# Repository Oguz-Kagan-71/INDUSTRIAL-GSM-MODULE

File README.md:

# INDUSTRIAL-GSM-MODULE
**PROJE KAZANIMLARI**
- Farklı amaca hizmet eden modüllerin datasheetini okuma
- Projeye uygun modül ve komponent seçimi
- Beslemelerde koruma amaçlı kullanılan kapasitör, endüktör, tvs diyot vb komponentlerin kullanımı
- PCB design edilen programda çoklu şematik pencere kullanımı, global label vb özelliklerin aktif kullanımı
- Kütüphanede olmayan komponentlerin şematik ve footprint kütüphanelerini datasheet bilgilerine göre oluşturup ekleme
- RS485 iletişim standartının ne olduğu ve hangi alanda kullanıldığı
- Transciever nedir ? Nasıl kullanılır ?
- Buck converter nedir ? Nasıl tasarlanır ?
- Yüksek voltaj kullanılan bir projede tasarım nasıl olmalıdır ? Regüle edilirken kullanılan komponentler nasıl konumlandırılmalıdır ?
- Konnektörler nasıl konumlandırılmalıdır ?
- Bağlantı kalınlıkları nasıl olmalıdır ?
- Anten bağlantısı nasıl olmalıdır ?
- Haberleşme bağlantıları nasıl olmalıdır ?
- GSM modülü nasıl çalışır ? Hangi amaca hizmet eder ?
- Modbus protokolü nedir ? Diğer haberleşme türlerinden farkı nedir ?
- 
-

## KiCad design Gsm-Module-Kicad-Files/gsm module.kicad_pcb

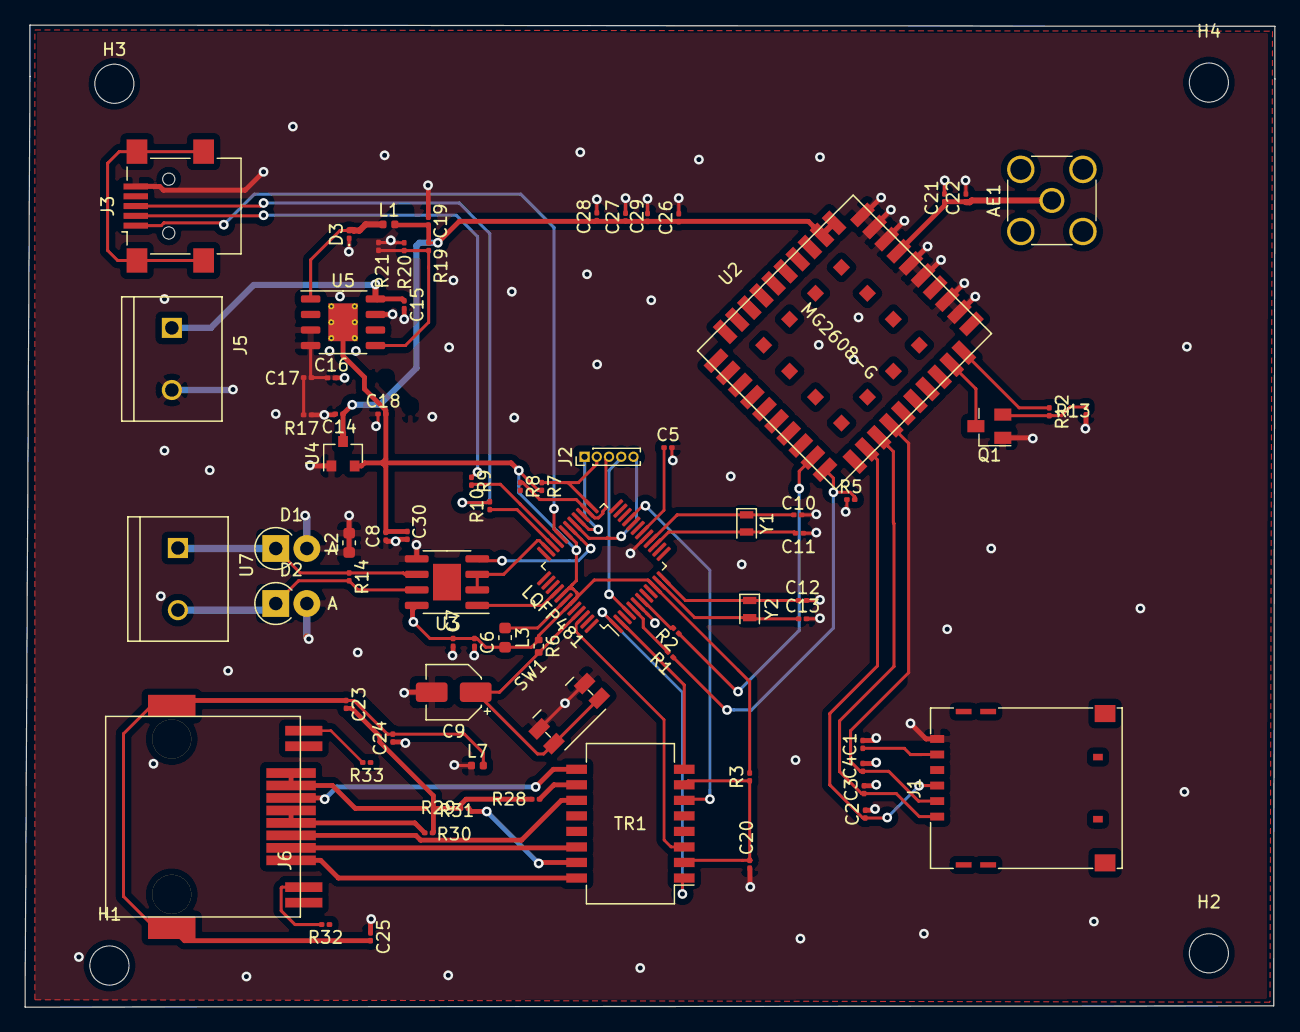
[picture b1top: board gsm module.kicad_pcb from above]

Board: 2 copper layers, 102.2 x 80.3 mm, 80 parts (0 on the bottom side), 59 nets.

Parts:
AE1: Antenna; SMA_Amphenol_132291_Vertical
C1: 0.1u; C_0201_0603Metric
C2, C3, C4, C21, C22, C29: 33p; C_0201_0603Metric
C5, C6, C7, C8: 0.1uF; C_0201_0603Metric
C9: 10uF/10V; CP_Elec_4x3
C10, C11, C12, C13: 20p; C_0201_0603Metric
C14, C18: 220nF; C_0201_0603Metric
C15: 10uF; C_0201_0603Metric
C16: 220uF; C_0201_0603Metric
C17: 22nF; C_0201_0603Metric
C19: 330uF; C_0201_0603Metric
C20: 220n; C_0201_0603Metric
C23: 1nF; C_0201_0603Metric
C24, C25: 100uF; C_0201_0603Metric
C26: 100u; C_0201_0603Metric
C27: 100n; C_0201_0603Metric
C28: 10p; C_0201_0603Metric
C30: 10u; C_0201_0603Metric
D1, D2: D_Schottky; D_DO-41_SOD81_P2.54mm_Vertical_AnodeUp
D3: DIODE; D_0201_0603Metric
H1, H2, H3, H4: MountingHole; MountingHole_3.2mm_M3
J1: SIM_Card; microSIM_JAE_SF53S006VCBR2000
J2: Conn_01x05_Male; PinHeader_1x05_P1.00mm_Vertical
J3: USB_OTG; USB_Mini-B_Lumberg_2486_01_Horizontal
J5: Conn_01x02_Male; TE_282837-2
J6: 8P8C_LED_Shielded; Würth_RJ45_SMD
L1: 33H; L_0402_1005Metric
L2, L3: L_Ferrite; L_0603_1608Metric
L7: 3H; L_0402_1005Metric
LQFP481: NUC126LG4AE; LQFP-48_7x7mm_P0.5mm
Q1: 2N2219; SuperSOT-3
R1, R2: 1k; R_0201_0603Metric
R3: 0; R_0201_0603Metric
R5: 5.6K; R_0201_0603Metric
R6: 10K; R_0402_1005Metric
R7, R8: 100K; R_0201_0603Metric
R9, R10: 33R; R_0201_0603Metric
R12, R17, R20, R21: 4.7k; R_0201_0603Metric
R13: 47k; R_0201_0603Metric
R14: 120R; R_0201_0603Metric
R19: 5.6k; R_0201_0603Metric
R28, R29, R30, R31: 75; R_0201_0603Metric
R32, R33: 220; R_0201_0603Metric
SW1: SW_Push; Panasonic_EVQPUJ_EVQPUA
TR1: PT61017PEL; Transformer_Ethernet_Bourns_PT61017PEL
U2: MG2608; MG2608-G
U3: SN65HVD10; SOIC-8-1EP_3.9x4.9mm_P1.27mm_EP2.29x3mm
U4: MCP1700-1202E_SOT23; SOT-23
U5: L5973D; HSOP-8-1EP_3.9x4.9mm_P1.27mm_EP2.41x3.1mm_ThermalVias
U7: klemens-2; TE_282837-2
Y1: 4-24 Mhz; Crystal_SMD_2012-2Pin_2.0x1.2mm
Y2: 32.768kHz; Crystal_SMD_2012-2Pin_2.0x1.2mm

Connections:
+3V3: C6.1, C7.1, C8.2, C18.1, C30.2, L3.2, LQFP481.10, LQFP481.31, LQFP481.41, LQFP481.43, R3.2, R6.1, R7.2, R8.2, U3.8, U4.2, U5.9
+4V: C14.1, C19.1, C26.1, C27.1, C28.1, C29.2, L1.2, R19.1, U2.31, U2.32, U4.3
/ethernet/SHİELD: C23.1, C24.2, C25.2, J6.SH, L7.2
GND: C1.2, C2.2, C3.2, C4.2, C5.2, C6.2, C7.2, C8.1, C9.2, C10.2, C11.2, C12.2, C13.2, C14.2, C15.2, C16.2, C18.2, C19.2, C20.1, C21.2, C22.2, C24.1, C25.1, C26.2, C27.2, C28.2, C29.1, C30.1, D1.2, D2.2, D3.1, J1.5, J3.5, J5.2, L2.1, L2.2, L7.1, LQFP481.6, LQFP481.17, Q1.1, R5.1, R13.1, R17.2, R20.2, R21.2, SW1.1, U2.22, U2.23, U2.25, U2.26, U2.28, U2.29, U2.30, U3.5, U4.1, U5.3, U5.7
unnamed: AE1.1, C21.1, C22.1, U2.27
unnamed: C5.1, LQFP481.18
unnamed: C9.1, LQFP481.45, R6.2, SW1.2
unnamed: C10.1, LQFP481.16, Y1.1
unnamed: C11.1, LQFP481.15, Y1.2
unnamed: C12.1, LQFP481.12, Y2.1
unnamed: C13.1, LQFP481.11, Y2.2
unnamed: C15.1, J5.1, U5.8
unnamed: C16.1, C17.1, U5.4
unnamed: C17.2, R17.1
unnamed: C20.2, R3.1, TR1.2, TR1.7
unnamed: C23.2, R28.2, R29.2, R30.2, R31.2
unnamed: D1.1, R14.1, U3.6, U7.1
unnamed: D2.1, R14.2, U3.7, U7.2
unnamed: D3.2, L1.1, U5.1
unnamed: J2.1, LQFP481.28
unnamed: J2.2, LQFP481.25, R7.1
unnamed: J2.3, LQFP481.26, R8.1
unnamed: J2.4, LQFP481.4
unnamed: J2.5, LQFP481.29
unnamed: J3.1, LQFP481.32
unnamed: J3.2, R9.1
unnamed: J3.3, R10.2
unnamed: J6.1, TR1.16
unnamed: J6.2, TR1.14
unnamed: J6.3, TR1.11
unnamed: J6.4, J6.5, R30.1
unnamed: J6.6, TR1.9
unnamed: J6.7, J6.8, R31.1
unnamed: J6.9, R33.2
unnamed: J6.11, R32.2
unnamed: L3.1, LQFP481.42
unnamed: LQFP481.33, R9.2
unnamed: LQFP481.34, R10.1
unnamed: Q1.2, R12.2, R13.2
unnamed: Q1.3, U2.19
unnamed: R1.1, R5.2, U2.10
unnamed: R2.1, U2.9
unnamed: R12.1, U2.20
unnamed: R19.2, R20.1, R21.1, U5.5
unnamed: R28.1, TR1.10
unnamed: R29.1, TR1.15
RE_DE_IO: LQFP481.35, U3.2, U3.3
RS_RX: LQFP481.40, U3.1
RS_TX: LQFP481.30, U3.4
RXN-ETH: LQFP481.2, TR1.8
RXP-ETH: LQFP481.21, TR1.6
SIM_CLK: C3.1, J1.3, U2.13
SIM_DATA: C4.1, J1.7, U2.14
SIM_RES: C2.1, J1.2, U2.12
SIM_VDD: C1.1, J1.1
TXN-ETH: LQFP481.46, TR1.3
TXP-ETH: LQFP481.1, TR1.1
UART_RX: LQFP481.7, R2.2
UART_TX: LQFP481.5, R1.2

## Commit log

2021-08-04 last version
2021-08-04 datasheet
2021-08-04 Datasheets
2021-08-06 Update gsm module.kicad_pcb
    PCB measure edit
2021-08-12 edited
2021-08-12 edit
